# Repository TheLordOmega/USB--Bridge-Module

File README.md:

# USB Bridge Module 

A module that forwards controller input received over the console's J1 bus
out to a phone, laptop, or SBC as a standard USB HID gamepad.

Key features:
* Receives button/stick state from the console over UART (J1)
* Presents as a real USB HID gamepad to whatever it's plugged into
* Built on an unmodified, pre-routed RP2040 gamepad PCB design (not a
  from-scratch board).

## PCB
for the PCB, i used the DIY-Portrait-mode-Gamepad as a reference but eavily modified it to fit my needs

## Schematic

## 3D Case

## Bill of Materials (excluding console)

Also found in [bom.csv](./bom.csv).

| Item                                                  | Price per unit                      | Nr of units | Total price | Link                                               |
| ----------------------------------------------------- | ----------------------------------- | ----------- | ----------- | -------------------------------------------------- |
| PCB                                                   |                                     | 1           | 20$         | -                                                  |
| 2x7 2.54mm pin header (J1 breakout board)             | ~$0.20-0.39                         | 1           | ~$0.20-0.39 | https://www.aliexpress.com/item/4000186187780.html |
| 3-pin flying-lead connector (JST-PH or Dupont header) |     -                               | 1           | -           | -                                                  |
| MD0/MD1 ID resistors, 0603                            |      -                              | 2           | -           | -                                                  |
| USB-C cable (to phone/laptop/SBC)                     |       1$                            | 1           | -           | -                                                  |
| **Total**                                             |                                     |             | 22$         |                                                    |

## Credits

* PCB design, case design, and gamepad reference layout (flash/crystal/
  regulator/USB-C circuit): [CoretechR/DIY-Portrait-Mode-Gamepad](https://github.com/CoretechR/DIY-Portrait-Mode-Gamepad),
  by Maximilian Kern
* USB device HID gamepad firmware base: [TinyUSB](https://github.com/hathach/tinyusb),
  `examples/device/hid_composite/src/main.c`, by hathach and contributors
* Console-side UART driver pattern:   [`wardriving-driver`](https://docs.rs/crate/wardriving-driver) crate's UART bus usage
* Driver: [`xpanse_api`](https://docs.rs/xpanse-api)
* Thanks to Hack Club and the Hackxpansion team for the console platform this module plugs into: https://github.com/hackclub/hackxpansion

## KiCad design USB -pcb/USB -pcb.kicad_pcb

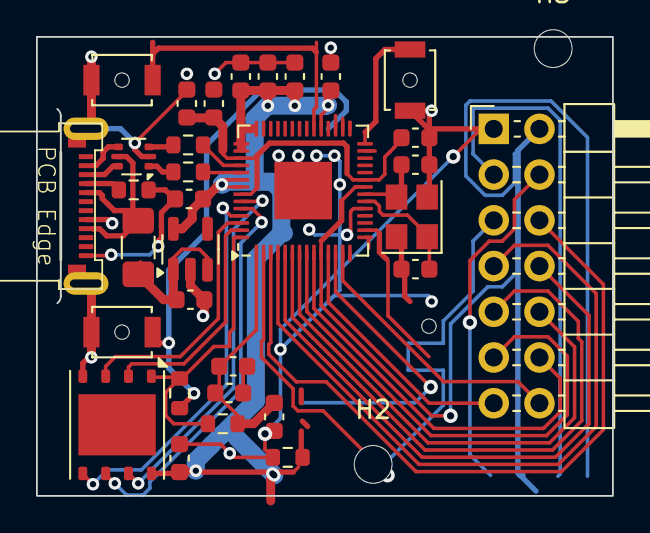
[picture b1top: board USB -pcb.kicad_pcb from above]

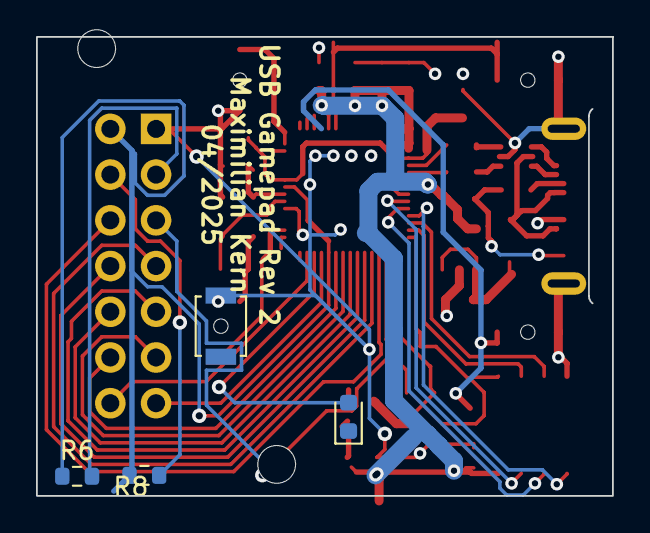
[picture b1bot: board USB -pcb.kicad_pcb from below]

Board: 2 copper layers, 32.0 x 25.5 mm, 38 parts (4 on the bottom side), 38 nets.

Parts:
C1, C2, C3, C11, C13: 1uF; C_0603_1608Metric
C4, C7, C8, C9, C10, C12, C14, C15: 100nF; C_0603_1608Metric
C5, C6: 15pF; C_0603_1608Metric
D1: LED; LED_0603_1608Metric
F1: 500mA; Fuse_1206_3216Metric_Pad1.42x1.75mm_HandSolder
H2, H3: MountingHole; MountingHole_2.1mm
J1: USB_C_Receptacle_USB2.0; USB_TYPEC_PLUG_12P
J2: Male_Module
R1: 10k; R_0603_1608Metric
R2: 1k; R_0603_1608Metric
R3, R4: 27; R_0603_1608Metric
R5: 2k2; R_0603_1608Metric
R6, R8: R; R_0603_1608Metric
R7: 5.1k; R_0603_1608Metric
SW11, SW12, SW13, SW14: SW_Push; SW_SPST_B3U-1000P-B
U1: AP2112K-3.3; SOT-23-5
U2: USBLC6-2P6; SOT-666
U3: W25Q64JVZPIQ; WSON-8-1EP_6x5mm_P1.27mm_EP3.4x4.3mm
U4: RP2040; QFN-56-1EP_7x7mm_P0.4mm_EP3.2x3.2mm
Y1: ABM8-272-T3; Crystal_SMD_Abracon_ABM8G-4Pin_3.2x2.5mm

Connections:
+1V1: C11.1, C14.1, C15.1, U4.23 (DVDD), U4.45 (VREG_VOUT), U4.50 (DVDD)
+3.3V: C2.1, C3.1, C4.1, C7.1, C8.1, C9.1, C10.1, C12.1, C13.1, J2.2 (3V3), R1.1, R6.1, R8.1, U1.5 (VOUT), U3.8 (VCC), U4.1 (IOVDD), U4.10 (IOVDD), U4.22 (IOVDD), U4.33 (IOVDD), U4.42 (IOVDD), U4.43 (ADC_AVDD), U4.44 (VREG_IN), U4.48 (USB_VDD), U4.49 (IOVDD)
/BT_A1: R2.2, SW13.1, U4.32 (GPIO21)
/BT_A2: SW14.1, U4.34 (GPIO22)
/BT_S1: SW11.1, U4.16 (GPIO13)
/BT_S2: SW12.1, U4.28 (GPIO17)
/D_N: J1.A7 (D-), U2.4 (I/O2)
/D_P: J1.A6 (D+), U2.6 (I/O1)
/Gpio0: J2.5 (GPIO0), U4.2 (GPIO0)
/Gpio1: J2.6 (GPIO1), U4.3 (GPIO1)
/Gpio2: J2.7 (GPI02), U4.4 (GPIO2)
/Gpio3: J2.8 (GPIO3), U4.5 (GPIO3)
/Gpio4: J2.9 (GPIO4), U4.6 (GPIO4)
/Gpio5: J2.10 (GPIO5), U4.7 (GPIO5)
/Gpio6: J2.11 (GPIO6), U4.8 (GPIO6)
/Gpio7: J2.12 (GPIO7), U4.9 (GPIO7)
/Gpio8: J2.13 (GPIO8), U4.11 (GPIO8)
/Gpio9: J2.14 (GPIO9), U4.13 (GPIO10)
/USB_D2_N: R4.1, U4.46 (USB_DM)
/USB_D2_P: R3.1, U4.47 (USB_DP)
/VUSB_RAW: F1.1, J1.A4 (VBUS), J1.B9 (VBUS), U2.5 (VBUS)
GND: C1.2, C2.2, C3.2, C4.2, C5.2, C6.1, C7.2, C8.2, C9.2, C10.2, C11.2, C12.2, C13.2, C14.2, C15.2, J1.A1 (GND), J1.A12 (GND), J1.B12 (GND), J1.S1 (SHIELD), J2.1 (GND), R5.1, R7.1, SW11.2, SW12.2, SW13.2, SW14.2, U1.2 (GND), U2.2 (GND), U3.4 (GND), U4.19 (TESTEN), U4.57 (GND), Y1.2, Y1.4
unnamed: D1.2 (A), U4.12 (GPIO9)
unnamed: D1.1 (K), R5.2
unnamed: J1.A5 (CC), R7.2
unnamed: J2.3 (MD0), R6.2
unnamed: J2.4 (MD1), R8.2
unnamed: C1.1, F1.2, U1.1 (VIN), U1.3 (EN)
unnamed: C5.1, U4.20 (XIN), Y1.1
unnamed: C6.2, U4.21 (XOUT), Y1.3
QSPI_CS: R1.2, R2.1, U3.1 (~CS), U4.56 (QSPI_SS)
QSPI_SCLK: U3.6 (CLK), U4.52 (QSPI_SCLK)
QSPI_SD0: U3.5 (DI(IO0)), U4.53 (QSPI_SD0)
QSPI_SD1: U3.2 (DO(IO1)), U4.55 (QSPI_SD1)
QSPI_SD2: U3.3 (IO2), U4.54 (QSPI_SD2)
QSPI_SD3: U3.7 (IO3), U4.51 (QSPI_SD3)
USB_D_N: R4.2, U2.3 (I/O2)
USB_D_P: R3.2, U2.1 (I/O1)
